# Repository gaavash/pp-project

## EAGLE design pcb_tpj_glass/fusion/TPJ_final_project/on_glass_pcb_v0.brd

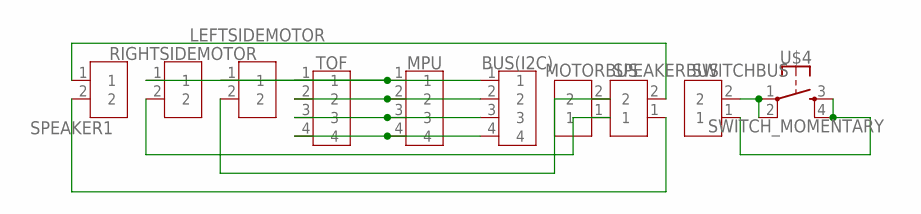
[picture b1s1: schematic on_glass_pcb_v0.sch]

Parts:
BUS(I2C): JST-XH-4PIN; B4B-XH-A
LEFTSIDEMOTOR: JST-VH-2PIN; B2P-VH_396-2N
MOTORBUS: JST-VH-2PIN; B2P-VH_396-2N
MPU: JST-XH-4PIN; B4B-XH-A
RIGHTSIDEMOTOR: JST-VH-2PIN; B2P-VH_396-2N
SPEAKER1: JST-VH-2PIN; B2P-VH_396-2N
SPEAKERBUS: JST-VH-2PIN; B2P-VH_396-2N
SWITCHBUS: JST-VH-2PIN; B2P-VH_396-2N
TOF: JST-XH-4PIN; B4B-XH-A
U$4: SWITCH_MOMENTARY; SWITCH-MOMENTARY-PTH-6.5MM

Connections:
unnamed: BUS(I2C).1, LEFTSIDEMOTOR.1, MPU.1, RIGHTSIDEMOTOR.1, TOF.1
unnamed: MOTORBUS.1, RIGHTSIDEMOTOR.2
unnamed: BUS(I2C).3, MPU.3, TOF.3
unnamed: BUS(I2C).4, MPU.4, TOF.4
unnamed: SPEAKER1.2, SPEAKERBUS.1
unnamed: SPEAKER1.1, SPEAKERBUS.2
unnamed: SWITCHBUS.2, U$4.1, U$4.2
unnamed: SWITCHBUS.1, U$4.3, U$4.4
unnamed: LEFTSIDEMOTOR.2, MOTORBUS.2
unnamed: BUS(I2C).2, MPU.2, TOF.2

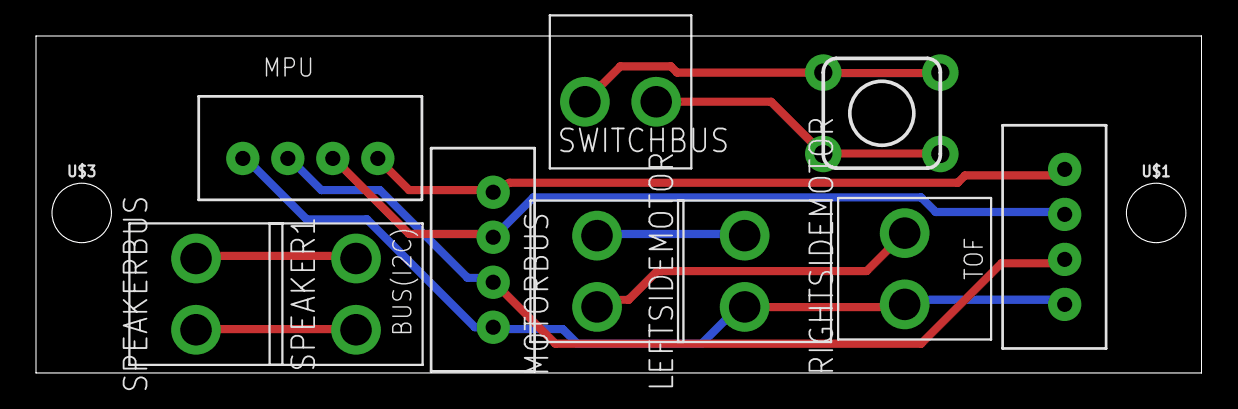
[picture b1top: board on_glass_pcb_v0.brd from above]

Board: 2 copper layers, 64.8 x 18.7 mm, 12 parts (0 on the bottom side), 10 nets.

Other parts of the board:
U$1, U$3: STAND-OFF

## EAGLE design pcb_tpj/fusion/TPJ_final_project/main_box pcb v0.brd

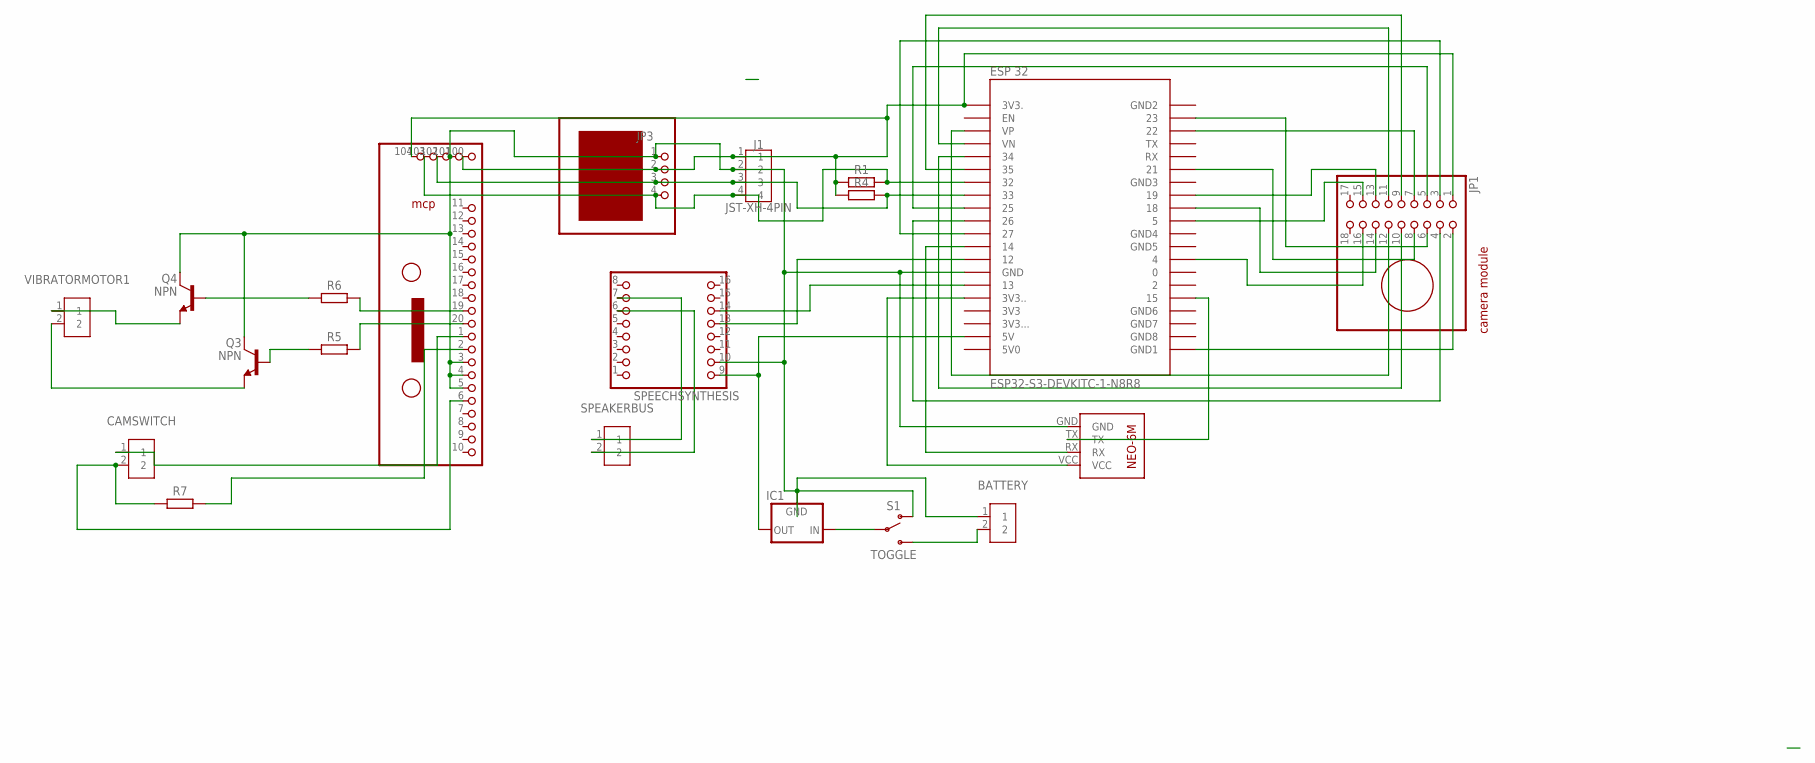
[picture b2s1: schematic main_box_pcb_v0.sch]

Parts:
BATTERY: JST-VH-2PIN; B2P-VH_396-2N
CAMSWITCH: JST-VH-2PIN; B2P-VH_396-2N
IC1: 78MXXS
J1: JST-XH-4PIN; B4B-XH-A
JP1: PINHD-2X9; 2X09
JP3: PINHD-1X4; 1X04
JP5: PINHD-1X10; 1X10
Q3, Q4: NPN; TO92
R1, R4: RESISTOR__AXIAL-11.7MM-PITCH; RESAD1176W63L850D250B
R5, R6, R7: RESISTOR__AXIAL-7.2MM-PITCH; RESAD724W46L381D178B
S1: TOGGLE; SWITCH-SPDT-PTH-8.5X3.7MM
SPEAKERBUS: JST-VH-2PIN; B2P-VH_396-2N
SPEECHSYNTHESIS: PINHD-1X8; 1X08
U$1: ESP32-S3-DEVKITC-1-N8R8
U$2: NEO-6M
VIBRATORMOTOR1: JST-VH-2PIN; B2P-VH_396-2N

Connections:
5V0: U$1.J1_21 (5V0)
unnamed: IC1.OUT, SPEECHSYNTHESIS.9 (VCC), U$1.J1_20 (5V)
unnamed: JP1.2 (GND), U$1.J3_21 (GND1)
unnamed: JP1.3 (SIOC), U$1.J1_12 (27)
unnamed: JP1.4 (SIOD), U$1.J1_11 (26)
unnamed: JP1.5 (VSYNC), U$1.J1_10 (25)
unnamed: JP1.6 (HREF), U$1.J3_3 (23)
unnamed: JP1.7 (PCLK), U$1.J3_4 (22)
unnamed: JP1.8 (XCLK), U$1.J3_7 (21)
unnamed: JP1.9 (D9), U$1.J1_7 (35)
unnamed: JP1.10 (D8), U$1.J1_6 (34)
unnamed: JP1.11 (D7), U$1.J1_5 (VN)
unnamed: JP1.12 (D6), U$1.J1_4 (VP)
unnamed: JP1.13 (D5), U$1.J3_9 (19)
unnamed: JP1.14 (D4), U$1.J3_10 (18)
unnamed: JP1.15 (D2), U$1.J3_11 (5)
unnamed: JP1.16 (D1), U$1.J3_14 (4)
unnamed: U$1.J1_17 (3V3..), U$2.VCC
unnamed: J1.4, JP3.4, JP5.103 (4), R1.2, U$1.J1_8 (32)
unnamed: J1.3, JP3.3, JP5.102 (3), R4.2, U$1.J1_9 (33)
unnamed: SPEAKERBUS.1, SPEECHSYNTHESIS.7 (GND1)
unnamed: JP5.20 (PB0), R5.2
unnamed: JP5.19 (PB1), R6.2
unnamed: IC1.IN, S1.2
unnamed: U$1.J3_17 (15), U$2.TX
unnamed: U$1.J1_13 (14), U$2.RX
unnamed: BATTERY.2, S1.3 (S)
unnamed: SPEECHSYNTHESIS.13 (DAC_L), U$1.J1_14 (12)
unnamed: SPEECHSYNTHESIS.14 (SPK_1), U$1.J1_16 (13)
unnamed: BATTERY.1, IC1.GND, J1.2, JP3.1, JP5.3 (PA0), JP5.4 (PA1), JP5.5 (PA2), JP5.101 (2), Q3.3 (C), Q4.3 (C), S1.1 (O), SPEECHSYNTHESIS.10 (RX), U$1.J1_15 (GND), U$2.GND
unnamed: SPEAKERBUS.2, SPEECHSYNTHESIS.6 (IO_2)
unnamed: J1.1, JP1.1 (3.3), JP3.2, JP5.100 (1), JP5.104 (5), R1.1, R4.1, U$1.J1_2 (3V3.)
unnamed: Q4.2 (B), R6.1
unnamed: Q3.2 (B), R5.1
unnamed: Q3.1 (E), VIBRATORMOTOR1.2
unnamed: Q4.1 (E), VIBRATORMOTOR1.1
unnamed: CAMSWITCH.1, JP5.1 (VCC)
unnamed: JP5.2 (GND), R7.2
unnamed: CAMSWITCH.2, JP5.6 (PA3), R7.1

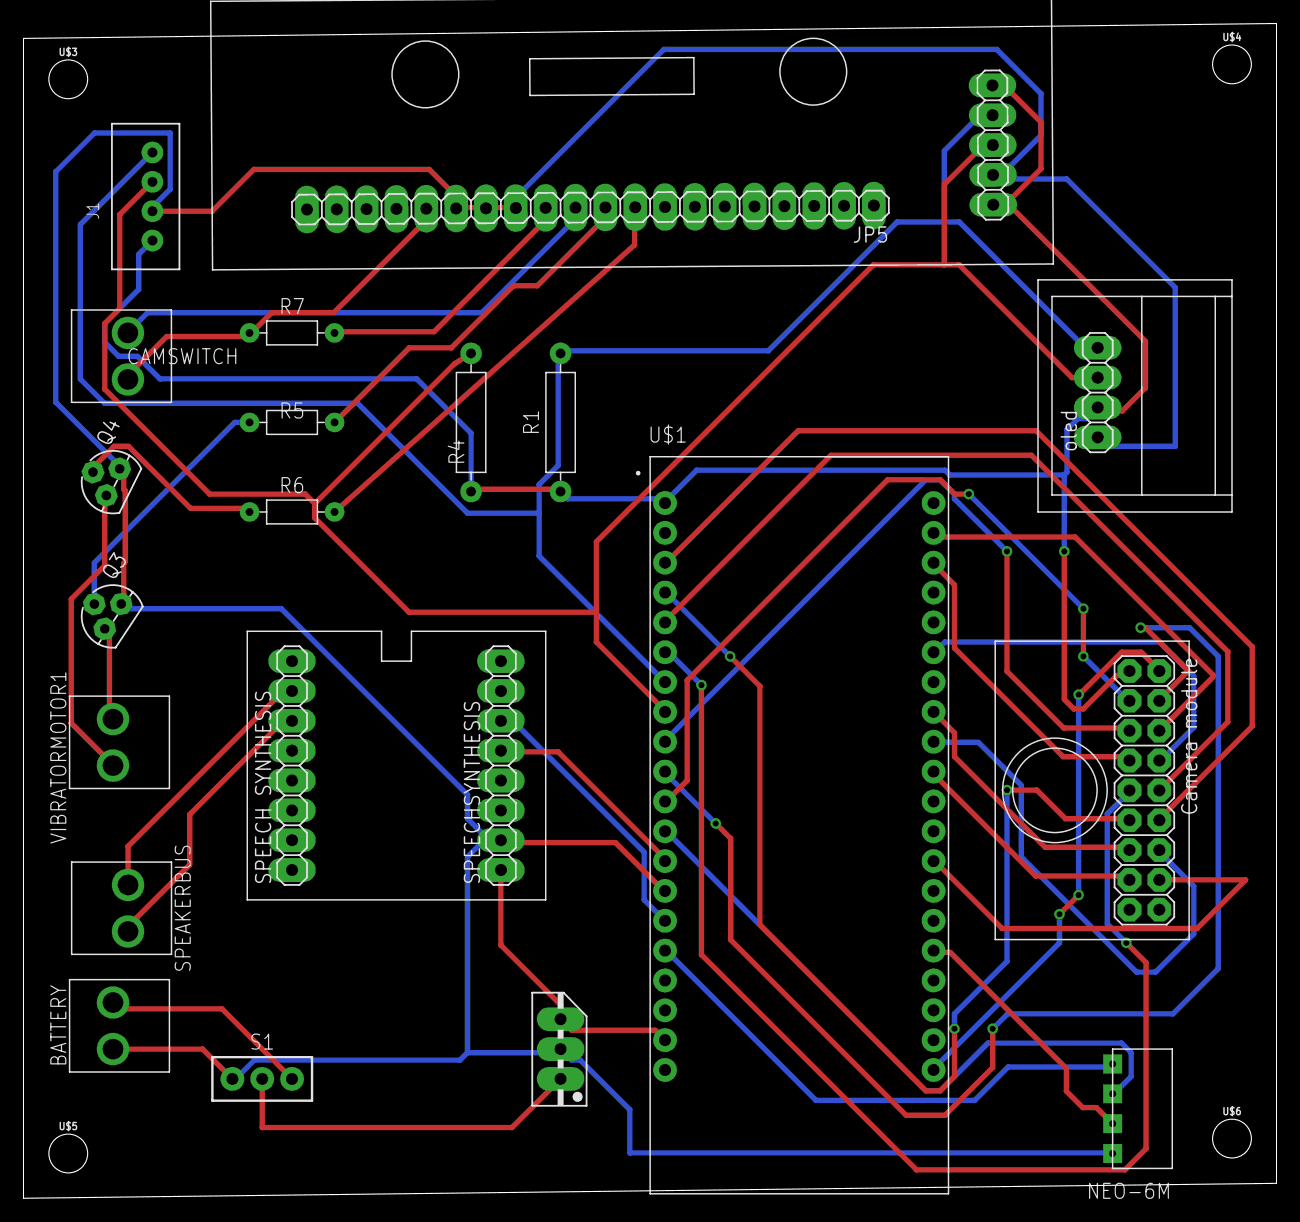
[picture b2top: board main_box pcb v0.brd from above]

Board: 2 copper layers, 106.7 x 100.0 mm, 24 parts (0 on the bottom side), 38 nets.

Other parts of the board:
U$3, U$4, U$5, U$6: STAND-OFF

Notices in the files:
parts and their libraries:
SparkFun-Hardware: Licensing: Creative Commons ShareAlike 4.0 International - https://creativecommons.org/licenses/by-sa/4.0
